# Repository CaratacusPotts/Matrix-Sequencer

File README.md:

# Matrix-Sequencer
**Stand Alone Midi Sequencer**, for immediate visual interaction with hardware synthesizers

## What
Midi sequencer designed to be easy to modify for beginners, and low cost to make.
Based on Arduino.

Operates in:
- Loop Mode
- Song Mode
- Conductor Mode

### Basic Functions (left row):
- Start/Stop: Play using internal clock or external midi clock
- BPM change using encoder
- Loop Start and End points via encoder
- Record:
  - Overtop: using Encoder button
  - On-Play: holding foot pedal, recording starts when first note played. Recording stops with foot off pedal. Automatically cuts loop to nearest beat, so loops nice.
- Clear notes (via encoder button)

### Canon and Note Functions (right rows):
- Transpose (to scale, on/off beat, via encoder or key input)
- Phase (by multiples of loop, by amount in steps)
- Frequency (compress note sequence in time, in fractions of current loop length)
- Mirror Notes Pitch (with a user defined mirror plane, reflect notes in pitch axis)
- Mirror Notes Loop (with a user defined mirror plane, reflect notes in time)
- Note Cutofff Filter (mute notes like a LPF or HPF)
- Note Velocity (use finger to draw note velocity or encoder)
- Note Duration (use encoder to increase or decrease all note lengths)

### Additional Features:
- 256 events (not bound by bars or specific steps)
- Polyphonic
- Intuitive scales

## [Specifications / Information Matrix V2 (encoder model)](MatrixV2/README.md)
## [Specifications / Information Matrix V1](MatrixV1/README.md)
## [Specifications / Informatoin Inline (simple midi looper)](Inline/README.md)

## Why
### Hardware synthesizer problem:

Electronic music possesses both its greatest asset and its greatest drawback: the unparalleled flexibility it offers in sound creation. It's simple to purchase a laptop, load your favourite DAW software, and then to wake up, after you have nodded off to a loop running endlessly in your headphones. Perhaps you may get lucky, and a fortuitous accidental mouse click during your slumber may result in a masterpiece. However, it is more probable that your music will end up sounding sterile.

Hardware synthesizers currently provide immediacy, tangibility, reliability and lack of spontaneous OS updates, that PC's cannot provide.  But without expensive hardware, the only way to quickly layer sounds is to use built in key-holds playing standard arpeggios that steadily erode their beauty through endless repetition of the same up/down sequences.

Goal was to:
- make an interface that allows for quick note controller access, with immediate visual and tactile feedback - with a nod to the Reason Matrix
- Keep cost low.  There are solutions already that do similar things, but start at £650 upwards. 
- Enhance workflow and notation in areas that typically do not get attention, that have a meaningful impact of the quality of music, such as instant: 
  - Transposing in key
  - Phasing
  - High-pass and Low-pass velocity muting
  - Canon functions in key (Crab, Inversion, Reversing etc)
  - Hardware agnostic 303 style accents and glides
  - Velocity and length control
- Composer mode, allowing the user to play a midi keyboard, and to be able to select which fingers play which synthesizer (for example: left pinky plays bass, middle finger lead, first 3 fingers strings etc)
- Record mode, where it starts the recording only when you play, and stops the recording and automatically trims length when you remove you foot.  This allows seemless live looping.
- Loops that are not bound by 16,32 or 64 steps.  But is only bound by number of events.  In the current state, this is 255 events, over a 32bit length of steps (which at low tempo could be a 10 min loop)
- Scale not chosen by archaic and unrelatable names.  Notes (key) chosen by just selecting which white and black note you want it to stay on - yes, that simple.  (Does not currently handle option to change base notes if going up or down like in a some melodic minor scales - to be added) 
- Open source and easy to modify for non-programmers to allow people to add features and tweak to their setup.  I really tried to avoid the use of pointers, classes, libraries etc, as I wanted this to be software that anyone could modify - worts and all (I failed on the Midi Library - need remove this at some point)
- Fit into existing setups without changing anything (inline).
- Assemble at home with basic SMD tools, and a 3D printer.

## Contents of the repository

I have tried to include everything I created on this project.

Please note: There are some schematic errors which required minor board mods!!  I have not got around to updating the PCB files.  Please see notes in folders for each item.

Files are for:
- Matrix (second one - with encoders built in)
- Inline looper
- Inline controller
- Matrix (first one - with not encoders)

Each folder contains:
- PCB schematics
- PCB Kicad files
- Arduino Code
- Azoteq touch files
- CAD files (plastic)
- BOM (mostly mouser parts)

#### Numbering style is me having fun..  

We really need to move to a base-12 system.  So so much better.  This is my base-12 numbering, using the super cool Pentomino. See https://en.wikipedia.org/wiki/Pentomino  (thank you Arthur C Clake for enlightening me)

This is my sequence below.  Using the beauty of base 12, like in music there are those lovely 4x3's.  You can see the pattern repeating and growing in complexity (5 is a slight mod of one, 6 of 2 and so on.  9 slight mod of 5, 10 of 6 and so on).  Tried to not have the shapes the same as western numbers.

More info here: [PENTOMINO](Pentomino/INFORMATION.md)

I also wanted the first numbers to grow dimensionally 1 side, 2 side, 3 side (also shown as triangle), 4 side (Pentomino cross is shown as a negative, as it looks better - and makes a square :-) ). 

## Photos

# Other Verions

## First Verison

## Inline Midi 

## Who
My name is Chris Malloy.  I developed the Hoverbike back in 2006.  For the last 10 years, my fantastic team and I have built a sucessful company that makes large heavy lift unmanned vehicles (company: Malloy Aeronautics www.malloyaeronautics.com )

I needed a break from that type of engineering, so whilst still helping the company, I have spent the last year finding time to work on this, and de-bug and have lots of fun playing on my gear.
If you want to listen to some very novice music made using this Matrix seqencer, see:
https://soundcloud.com/c-malloy

A Vimeo channel with a video of an earlier version of the Matrix

All the best

Chris

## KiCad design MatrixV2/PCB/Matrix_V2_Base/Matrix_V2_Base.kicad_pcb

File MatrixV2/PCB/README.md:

These files were created in Ki-cad.
Some of the pads are custom and need the footprints tweaking.
On the lower board (base), I don't recall any errors
On the upper board, I messed up on the PNP mosfet footprints(?), and the pins are wrong.  CHECK!!!, otherwise you will be doing what I did on this board and inverting and rotating the mosfets to get solder them.  Pain.

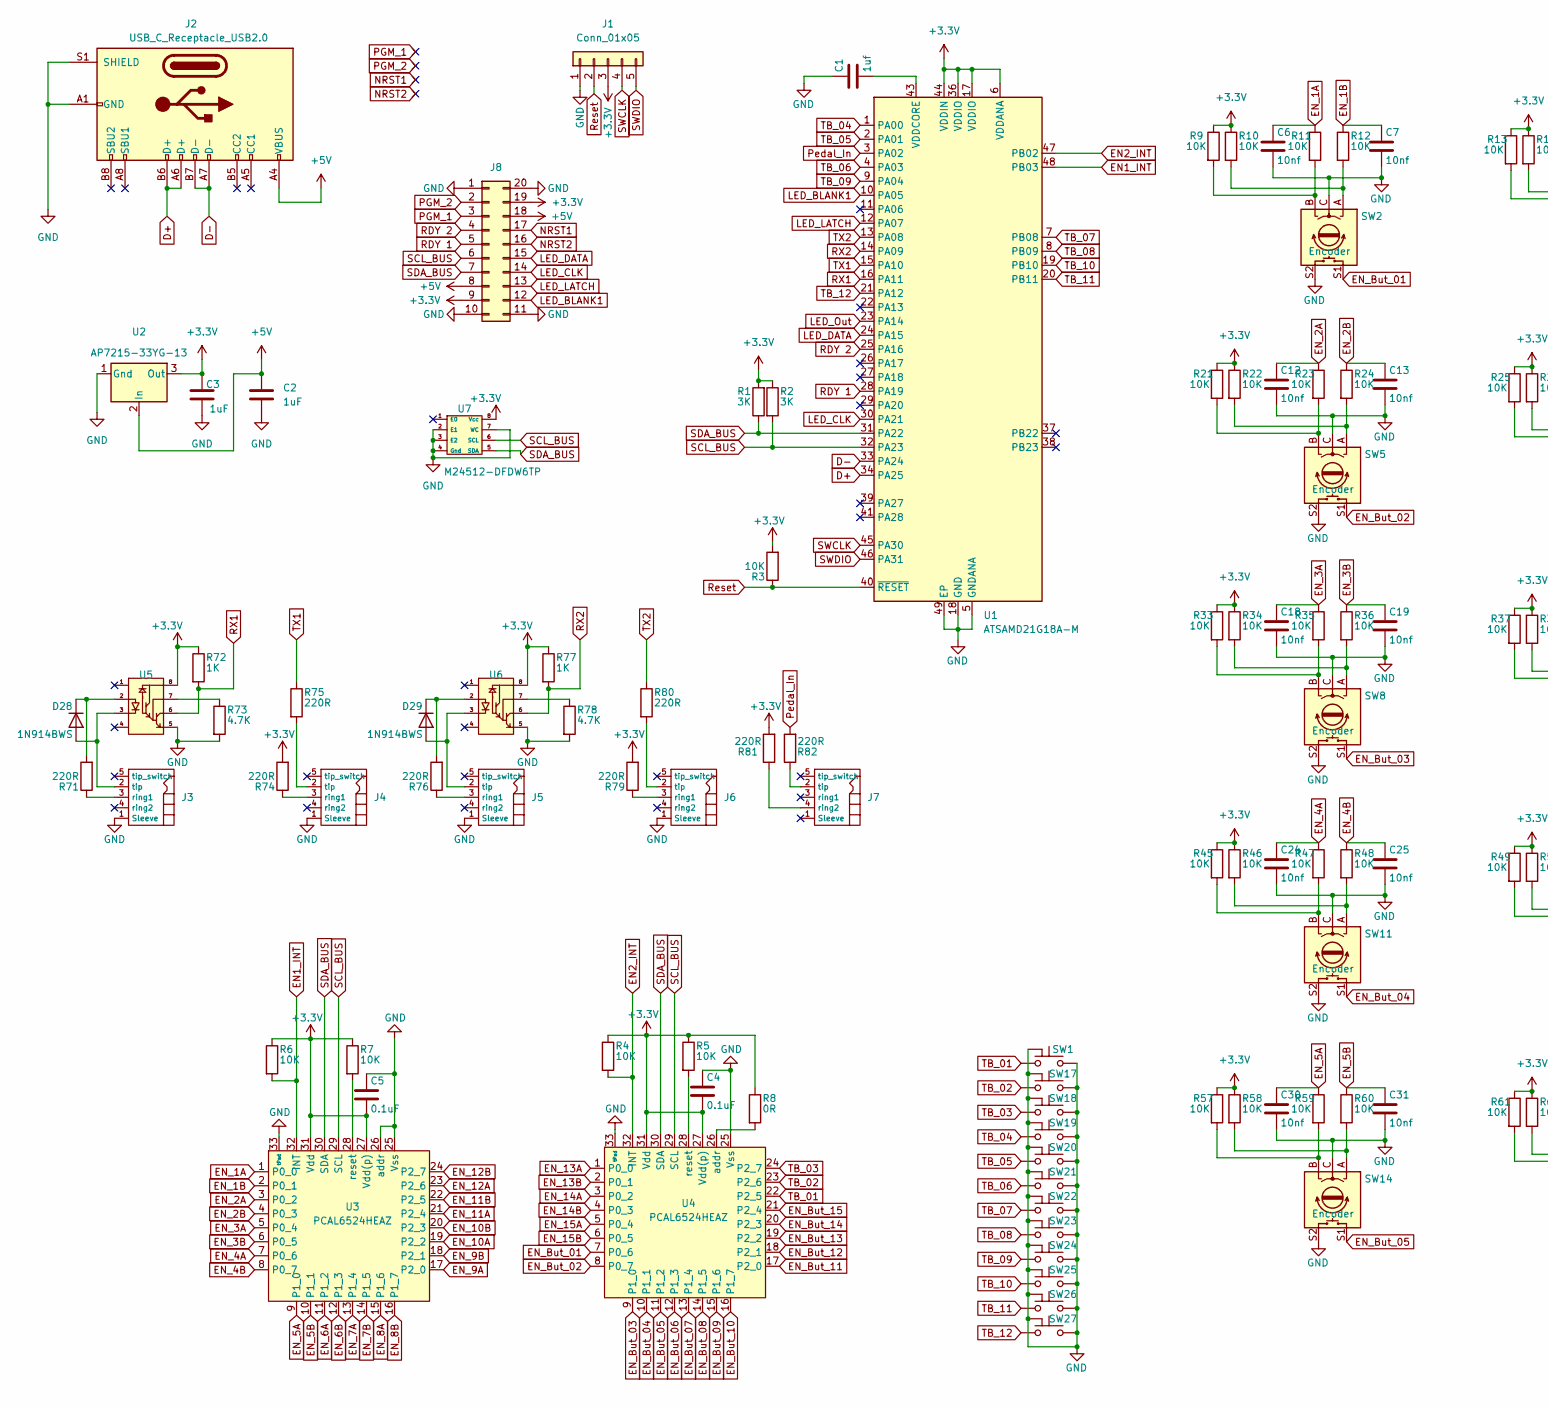
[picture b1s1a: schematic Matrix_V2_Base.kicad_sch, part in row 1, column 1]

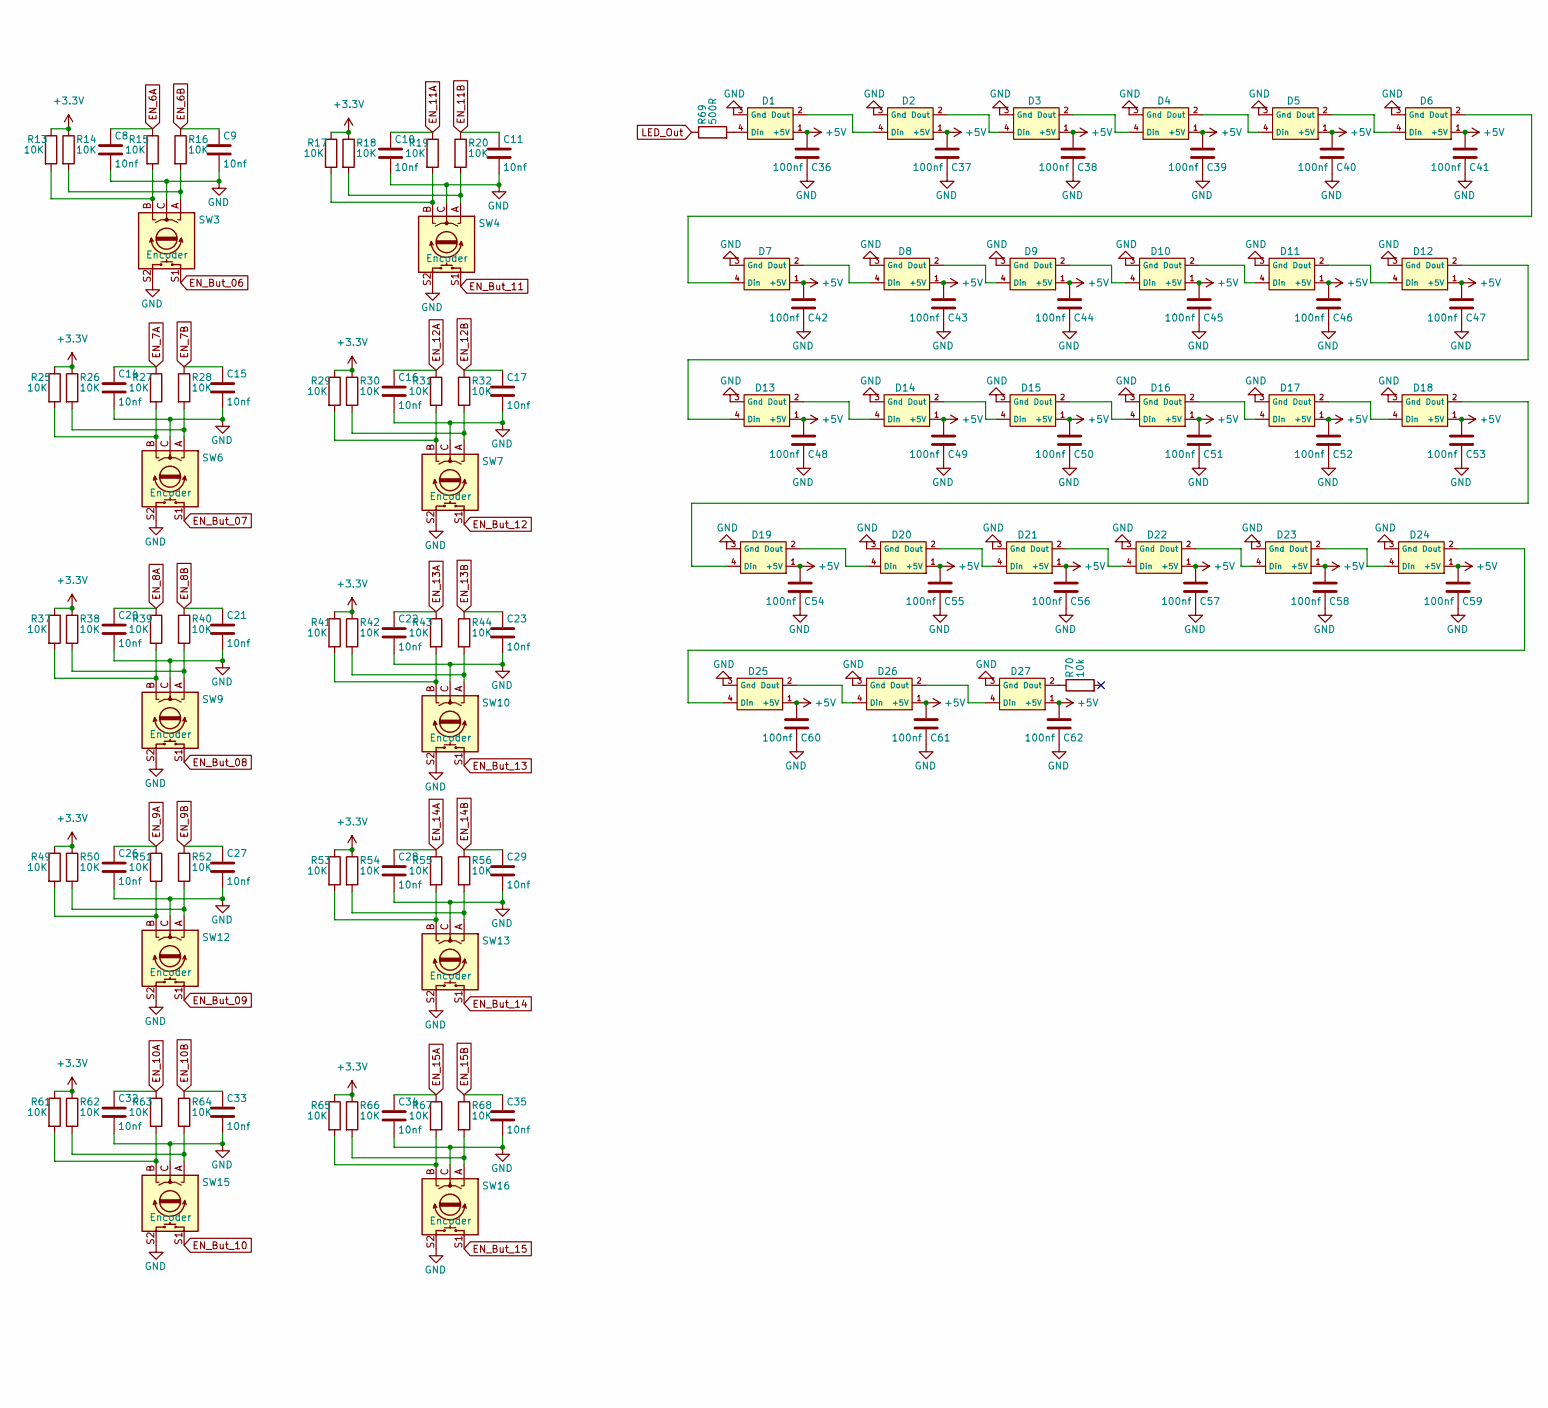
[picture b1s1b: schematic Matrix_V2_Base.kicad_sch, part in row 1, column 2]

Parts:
C1: 1uf; C_0603_1608Metric_Pad1.08x0.95mm_HandSolder
C2, C3: 1uF; C_0603_1608Metric_Pad1.08x0.95mm_HandSolder
C4, C5: 0.1uF; C_0603_1608Metric_Pad1.08x0.95mm_HandSolder
C6, C7, C8, C9, C10, C11, C12, C13, C14, C15, C16, C17, C18, C19, C20, C21, C22, C23, C24, C25, C26, C27, C28, C29, C30, C31, C32, C33, C34, C35: 10nf; C_0603_1608Metric_Pad1.08x0.95mm_HandSolder
C36, C37, C38, C39, C40, C41, C42, C43, C44, C45, C46, C47, C48, C49, C50, C51, C52, C53, C54, C55, C56, C57, C58, C59, C60, C61, C62: 100nf; C_0603_1608Metric_Pad1.08x0.95mm_HandSolder
D1, D2, D3, D4, D5, D6, D7, D8, D9, D10, D11, D12, D13, D14, D15, D16, D17, D18, D19, D20, D21, D22, D23, D24, D25, D26, D27: IN-PI55TATPRPGPB
D28, D29: 1N914BWS; D_SOD-523
J1: Conn_01x05; 5pin SMD ProgramPads
J2: USB_C_Receptacle_USB2.0; USB_C_Receptacle_XKB_U262-16XN-4BVC11
J3, J4, J5, J6, J7: SJ-43515TS-SMT-TR
J8: Conn_02x10_Counter_Clockwise; 10132798-022100LF
R1, R2: 3K; R_0805_2012Metric_Pad1.20x1.40mm_HandSolder
R3, R4, R5, R6, R7, R9, R10, R11, R12, R13, R14, R15, R16, R17, R18, R19, R20, R21, R22, R23, R24, R25, R26, R27, R28, R29, R30, R31, R32, R33, R34, R35, R36, R37, R38, R39, R40, R41, R42, R43, R44, R45, R46, R47, R48, R49, R50, R51, R52, R53, R54, R55, R56, R57, R58, R59, R60, R61, R62, R63, R64, R65, R66, R67, R68: 10K; R_0805_2012Metric_Pad1.20x1.40mm_HandSolder
R8: 0R; R_0805_2012Metric_Pad1.20x1.40mm_HandSolder
R69: 500R; R_0805_2012Metric_Pad1.20x1.40mm_HandSolder
R70: 10k; R_0805_2012Metric_Pad1.20x1.40mm_HandSolder
R71, R74, R75, R76, R79, R80, R81, R82: 220R; R_0805_2012Metric_Pad1.20x1.40mm_HandSolder
R72, R77: 1K; R_0805_2012Metric_Pad1.20x1.40mm_HandSolder
R73, R78: 4.7K; R_0805_2012Metric_Pad1.20x1.40mm_HandSolder
SW1, SW17, SW18, SW19, SW20, SW21, SW22, SW23, SW24, SW25, SW26, SW27: SW_Push; TS06-667-55-BK-100-G-SMT-TR
SW2, SW3, SW4, SW5, SW6, SW7, SW8, SW9, SW10, SW11, SW12, SW13, SW14, SW15, SW16: Encoder; PEC11S
U1: ATSAMD21G18A-M; QFN-48-1EP_7x7mm_P0.5mm_EP5.15x5.15mm
U2: AP7215-33YG-13; SOT-89-3
U3, U4: PCAL6524HEAZ; HUQFN32
U5, U6: SFH6318; SFH6318 SOIC-8
U7: M24512-DFDW6TP

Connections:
+3.3V: C3.1, C4.2, C5.2, J1.3, J8.9, J8.19, R1.2, R2.1, R3.2, R4.1, R5.1, R6.1, R7.1, R8.1, R9.1, R10.1, R13.1, R14.1, R17.1, R18.1, R21.1, R22.1, R25.1, R26.1, R29.1, R30.1, R33.1, R34.1, R37.1, R38.1, R41.1, R42.1, R45.1, R46.1, R49.1, R50.1, R53.1, R54.1, R57.1, R58.1, R61.1, R62.1, R65.1, R66.1, R72.1, R74.2, R77.1, R79.2, R81.2, U1.6 (VDDANA), U1.17 (VDDIO), U1.36 (VDDIO), U1.44 (VDDIN), U2.3 (Out), U3.27 (Vdd(p)), U3.31 (Vdd), U4.27 (Vdd(p)), U4.31 (Vdd), U5.8, U6.8, U7.8 (Vcc)
+5V: C2.1, C36.1, C37.1, C38.1, C39.1, C40.1, C41.1, C42.1, C43.1, C44.1, C45.1, C46.1, C47.1, C48.1, C49.1, C50.1, C51.1, C52.1, C53.1, C54.1, C55.1, C56.1, C57.1, C58.1, C59.1, C60.1, C61.1, C62.1, D1.1 (+5V), D2.1 (+5V), D3.1 (+5V), D4.1 (+5V), D5.1 (+5V), D6.1 (+5V), D7.1 (+5V), D8.1 (+5V), D9.1 (+5V), D10.1 (+5V), D11.1 (+5V), D12.1 (+5V), D13.1 (+5V), D14.1 (+5V), D15.1 (+5V), D16.1 (+5V), D17.1 (+5V), D18.1 (+5V), D19.1 (+5V), D20.1 (+5V), D21.1 (+5V), D22.1 (+5V), D23.1 (+5V), D24.1 (+5V), D25.1 (+5V), D26.1 (+5V), D27.1 (+5V), J2.A4 (VBUS), J2.A9 (VBUS), J2.B4 (VBUS), J2.B9 (VBUS), J8.8, J8.18, U2.2 (In)
D+: J2.A6 (D+), J2.B6 (D+), U1.34 (PA25)
D-: J2.A7 (D-), J2.B7 (D-), U1.33 (PA24)
EN1_INT: R6.2, U1.48 (PB03), U3.32 (INT)
EN2_INT: R4.2, U1.47 (PB02), U4.32 (INT)
EN_1A: C6.1, R11.1, U3.1 (P0_0)
EN_1B: C7.1, R12.1, U3.2 (P0_1)
EN_2A: C12.1, R23.1, U3.3 (P0_2)
EN_2B: C13.1, R24.1, U3.4 (P0_3)
EN_3A: C18.1, R35.1, U3.5 (P0_4)
EN_3B: C19.1, R36.1, U3.6 (P0_5)
EN_4A: C24.1, R47.1, U3.7 (P0_6)
EN_4B: C25.1, R48.1, U3.8 (P0_7)
EN_5A: C30.1, R59.1, U3.9 (P1_0)
EN_5B: C31.1, R60.1, U3.10 (P1_1)
EN_6A: C8.1, R15.1, U3.11 (P1_2)
EN_6B: C9.1, R16.1, U3.12 (P1_3)
EN_7A: C14.1, R27.1, U3.13 (P1_4)
EN_7B: C15.1, R28.1, U3.14 (P1_5)
EN_8A: C20.1, R39.1, U3.15 (P1_6)
EN_8B: C21.1, R40.1, U3.16 (P1_7)
EN_9A: C26.1, R51.1, U3.17 (P2_0)
EN_9B: C27.1, R52.1, U3.18 (P2_1)
EN_10A: C32.1, R63.1, U3.19 (P2_2)
EN_10B: C33.1, R64.1, U3.20 (P2_3)
EN_11A: C10.1, R19.1, U3.21 (P2_4)
EN_11B: C11.1, R20.1, U3.22 (P2_5)
EN_12A: C16.1, R31.1, U3.23 (P2_6)
EN_12B: C17.1, R32.1, U3.24 (P2_7)
EN_13A: C22.1, R43.1, U4.1 (P0_0)
EN_13B: C23.1, R44.1, U4.2 (P0_1)
EN_14A: C28.1, R55.1, U4.3 (P0_2)
EN_14B: C29.1, R56.1, U4.4 (P0_3)
EN_15A: C34.1, R67.1, U4.5 (P0_4)
EN_15B: C35.1, R68.1, U4.6 (P0_5)
EN_But_01: SW2.S1, U4.7 (P0_6)
EN_But_02: SW5.S1, U4.8 (P0_7)
EN_But_03: SW8.S1, U4.9 (P1_0)
EN_But_04: SW11.S1, U4.10 (P1_1)
EN_But_05: SW14.S1, U4.11 (P1_2)
EN_But_06: SW3.S1, U4.12 (P1_3)
EN_But_07: SW6.S1, U4.13 (P1_4)
EN_But_08: SW9.S1, U4.14 (P1_5)
EN_But_09: SW12.S1, U4.15 (P1_6)
EN_But_10: SW15.S1, U4.16 (P1_7)
EN_But_11: SW4.S1, U4.17 (P2_0)
EN_But_12: SW7.S1, U4.18 (P2_1)
EN_But_13: SW10.S1, U4.19 (P2_2)
EN_But_14: SW13.S1, U4.20 (P2_3)
EN_But_15: SW16.S1, U4.21 (P2_4)
GND: C1.1, C2.2, C3.2, C4.1, C5.1, C6.2, C7.2, C8.2, C9.2, C10.2, C11.2, C12.2, C13.2, C14.2, C15.2, C16.2, C17.2, C18.2, C19.2, C20.2, C21.2, C22.2, C23.2, C24.2, C25.2, C26.2, C27.2, C28.2, C29.2, C30.2, C31.2, C32.2, C33.2, C34.2, C35.2, C36.2, C37.2, C38.2, C39.2, C40.2, C41.2, C42.2, C43.2, C44.2, C45.2, C46.2, C47.2, C48.2, C49.2, C50.2, C51.2, C52.2, C53.2, C54.2, C55.2, C56.2, C57.2, C58.2, C59.2, C60.2, C61.2, C62.2, D1.3 (Gnd), D2.3 (Gnd), D3.3 (Gnd), D4.3 (Gnd), D5.3 (Gnd), D6.3 (Gnd), D7.3 (Gnd), D8.3 (Gnd), D9.3 (Gnd), D10.3 (Gnd), D11.3 (Gnd), D12.3 (Gnd), D13.3 (Gnd), D14.3 (Gnd), D15.3 (Gnd), D16.3 (Gnd), D17.3 (Gnd), D18.3 (Gnd), D19.3 (Gnd), D20.3 (Gnd), D21.3 (Gnd), D22.3 (Gnd), D23.3 (Gnd), D24.3 (Gnd), D25.3 (Gnd), D26.3 (Gnd), D27.3 (Gnd), J1.1, J2.A1 (GND), J2.A12 (GND), J2.B1 (GND), J2.B12 (GND), J2.S1 (SHIELD), J3.1 (Sleeve), J4.1 (Sleeve), J5.1 (Sleeve), J6.1 (Sleeve), J8.1, J8.10, J8.11, J8.20, R73.2, R78.2, SW1.2, SW1.3 (GND), SW2.C, SW2.S2, SW3.C, SW3.S2, SW4.C, SW4.S2, SW5.C, SW5.S2, SW6.C, SW6.S2, SW7.C, SW7.S2, SW8.C, SW8.S2, SW9.C, SW9.S2, SW10.C, SW10.S2, SW11.C, SW11.S2, SW12.C, SW12.S2, SW13.C, SW13.S2, SW14.C, SW14.S2, SW15.C, SW15.S2, SW16.C, SW16.S2, SW17.2, SW17.3 (GND), SW18.2, SW18.3 (GND), SW19.2, SW19.3 (GND), SW20.2, SW20.3 (GND), SW21.2, SW21.3 (GND), SW22.2, SW22.3 (GND), SW23.2, SW23.3 (GND), SW24.2, SW24.3 (GND), SW25.2, SW25.3 (GND), SW26.2, SW26.3 (GND), SW27.2, SW27.3 (GND), U1.5 (GNDANA), U1.18 (GND), U1.35 (GND), U1.42 (GND), U1.49 (EP), U2.1 (Gnd), U3.25 (Vss), U3.26 (addr), U3.33 (tPad), U4.25 (Vss), U4.33 (tPad), U5.5, U6.5, U7.2 (E1), U7.3 (E2), U7.4 (Gnd), U7.7 (WC)
LED_BLANK1: J8.12, U1.10 (PA05)
LED_CLK: J8.14, U1.30 (PA21)
LED_DATA: J8.15, U1.24 (PA15)
LED_LATCH: J8.13, U1.12 (PA07)
LED_Out: R69.1, U1.23 (PA14)
NRST1: J8.17
NRST2: J8.16
unnamed: C1.2, U1.43 (VDDCORE)
unnamed: D1.2 (Dout), D2.4 (Din)
unnamed: D1.4 (Din), R69.2
unnamed: D2.2 (Dout), D3.4 (Din)
unnamed: D3.2 (Dout), D4.4 (Din)
unnamed: D4.2 (Dout), D5.4 (Din)
unnamed: D5.2 (Dout), D6.4 (Din)
unnamed: D6.2 (Dout), D7.4 (Din)
unnamed: D7.2 (Dout), D8.4 (Din)
unnamed: D8.2 (Dout), D9.4 (Din)
unnamed: D10.2 (Dout), D11.4 (Din)
unnamed: D9.2 (Dout), D10.4 (Din)
unnamed: D11.2 (Dout), D12.4 (Din)
unnamed: D12.2 (Dout), D13.4 (Din)
unnamed: D13.2 (Dout), D14.4 (Din)
unnamed: D14.2 (Dout), D15.4 (Din)
unnamed: D15.2 (Dout), D16.4 (Din)
unnamed: D16.2 (Dout), D17.4 (Din)
unnamed: D17.2 (Dout), D18.4 (Din)
unnamed: D18.2 (Dout), D19.4 (Din)
unnamed: D19.2 (Dout), D20.4 (Din)
unnamed: D20.2 (Dout), D21.4 (Din)
unnamed: D21.2 (Dout), D22.4 (Din)
unnamed: D22.2 (Dout), D23.4 (Din)
unnamed: D23.2 (Dout), D24.4 (Din)
unnamed: D24.2 (Dout), D25.4 (Din)
unnamed: D25.2 (Dout), D26.4 (Din)
unnamed: D26.2 (Dout), D27.4 (Din)
unnamed: D27.2 (Dout), R70.1
unnamed: D28.1 (K), R71.2, U5.2
unnamed: D28.2 (A), J3.2 (tip), U5.3
unnamed: D29.1 (K), R76.2, U6.2
unnamed: D29.2 (A), J5.2 (tip), U6.3
unnamed: J3.3 (ring1), R71.1
unnamed: J4.2 (tip), R75.2
unnamed: J4.3 (ring1), R74.1
unnamed: J5.3 (ring1), R76.1
unnamed: J6.2 (tip), R80.2
unnamed: J6.3 (ring1), R79.1
unnamed: J7.2 (tip), R82.1
unnamed: J7.4 (ring2), R81.1
unnamed: R5.2, U4.28 (reset)
unnamed: R7.2, U3.28 (reset)
unnamed: R8.2, U4.26 (addr)
unnamed: R10.2, R12.2, SW2.A
unnamed: R9.2, R11.2, SW2.B
unnamed: R13.2, R15.2, SW3.B
unnamed: R14.2, R16.2, SW3.A
unnamed: R17.2, R19.2, SW4.B
unnamed: R18.2, R20.2, SW4.A
unnamed: R21.2, R23.2, SW5.B
unnamed: R22.2, R24.2, SW5.A
unnamed: R25.2, R27.2, SW6.B
unnamed: R26.2, R28.2, SW6.A
unnamed: R29.2, R31.2, SW7.B
unnamed: R30.2, R32.2, SW7.A
unnamed: R33.2, R35.2, SW8.B
unnamed: R34.2, R36.2, SW8.A
unnamed: R37.2, R39.2, SW9.B
unnamed: R38.2, R40.2, SW9.A
unnamed: R41.2, R43.2, SW10.B
unnamed: R42.2, R44.2, SW10.A
unnamed: R45.2, R47.2, SW11.B
unnamed: R46.2, R48.2, SW11.A
unnamed: R49.2, R51.2, SW12.B
unnamed: R50.2, R52.2, SW12.A
unnamed: R53.2, R55.2, SW13.B
unnamed: R54.2, R56.2, SW13.A
unnamed: R57.2, R59.2, SW14.B
unnamed: R58.2, R60.2, SW14.A
unnamed: R61.2, R63.2, SW15.B
unnamed: R62.2, R64.2, SW15.A
unnamed: R65.2, R67.2, SW16.B
unnamed: R66.2, R68.2, SW16.A
unnamed: R73.1, U5.7
unnamed: R78.1, U6.7
PGM_1: J8.3
PGM_2: J8.2
Pedal_In: R82.2, U1.3 (PA02)
RDY 1: J8.5, U1.28 (PA19)
RDY 2: J8.4, U1.25 (PA16)
RX1: R72.2, U1.16 (PA11), U5.6
RX2: R77.2, U1.14 (PA09), U6.6
Reset: J1.2, R3.1, U1.40 (~RESET)
SCL_BUS: J8.6, R2.2, U1.32 (PA23), U3.29 (SCL), U4.29 (SCL), U7.6 (SCL)
SDA_BUS: J8.7, R1.1, U1.31 (PA22), U3.30 (SDA), U4.30 (SDA), U7.5 (SDA)
SWCLK: J1.4, U1.45 (PA30)
SWDIO: J1.5, U1.46 (PA31)
TB_01: SW1.1, U4.22 (P2_5)
TB_02: SW17.1, U4.23 (P2_6)
TB_03: SW18.1, U4.24 (P2_7)
TB_04: SW19.1, U1.1 (PA00)
TB_05: SW20.1, U1.2 (PA01)
TB_06: SW21.1, U1.4 (PA03)
TB_07: SW22.1, U1.7 (PB08)
TB_08: SW23.1, U1.8 (PB09)
TB_09: SW24.1, U1.9 (PA04)
TB_10: SW25.1, U1.19 (PB10)
TB_11: SW26.1, U1.20 (PB11)
TB_12: SW27.1, U1.21 (PA12)
TX1: R75.1, U1.15 (PA10)
TX2: R80.1, U1.13 (PA08)

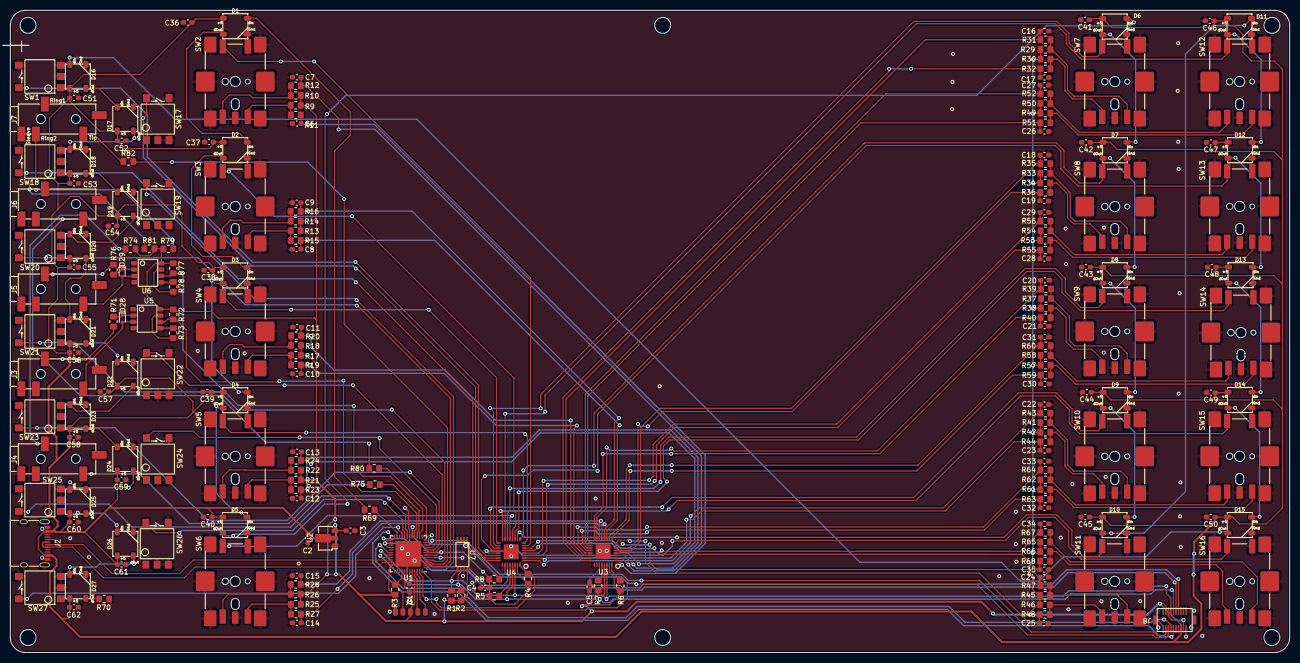
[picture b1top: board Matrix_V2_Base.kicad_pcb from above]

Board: 2 copper layers, 256.0 x 128.5 mm, 215 parts (0 on the bottom side), 157 nets.

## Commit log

2023-06-08 Create temp
2023-06-28 Create Instructions
